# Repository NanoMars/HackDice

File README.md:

# HackDice

## Schematic

## PCB

## Features
- Animated Dice rolling animation
- Displays a random side of a 6 sided dice on a custom LED 7 segment display
- USB C powered

## BOM
- 7 	LED's
- 7 	220 Resistor
- 1 	Push Button
- 1   Seeed XIAO RP2040

Made by `@Mars` on slack :D

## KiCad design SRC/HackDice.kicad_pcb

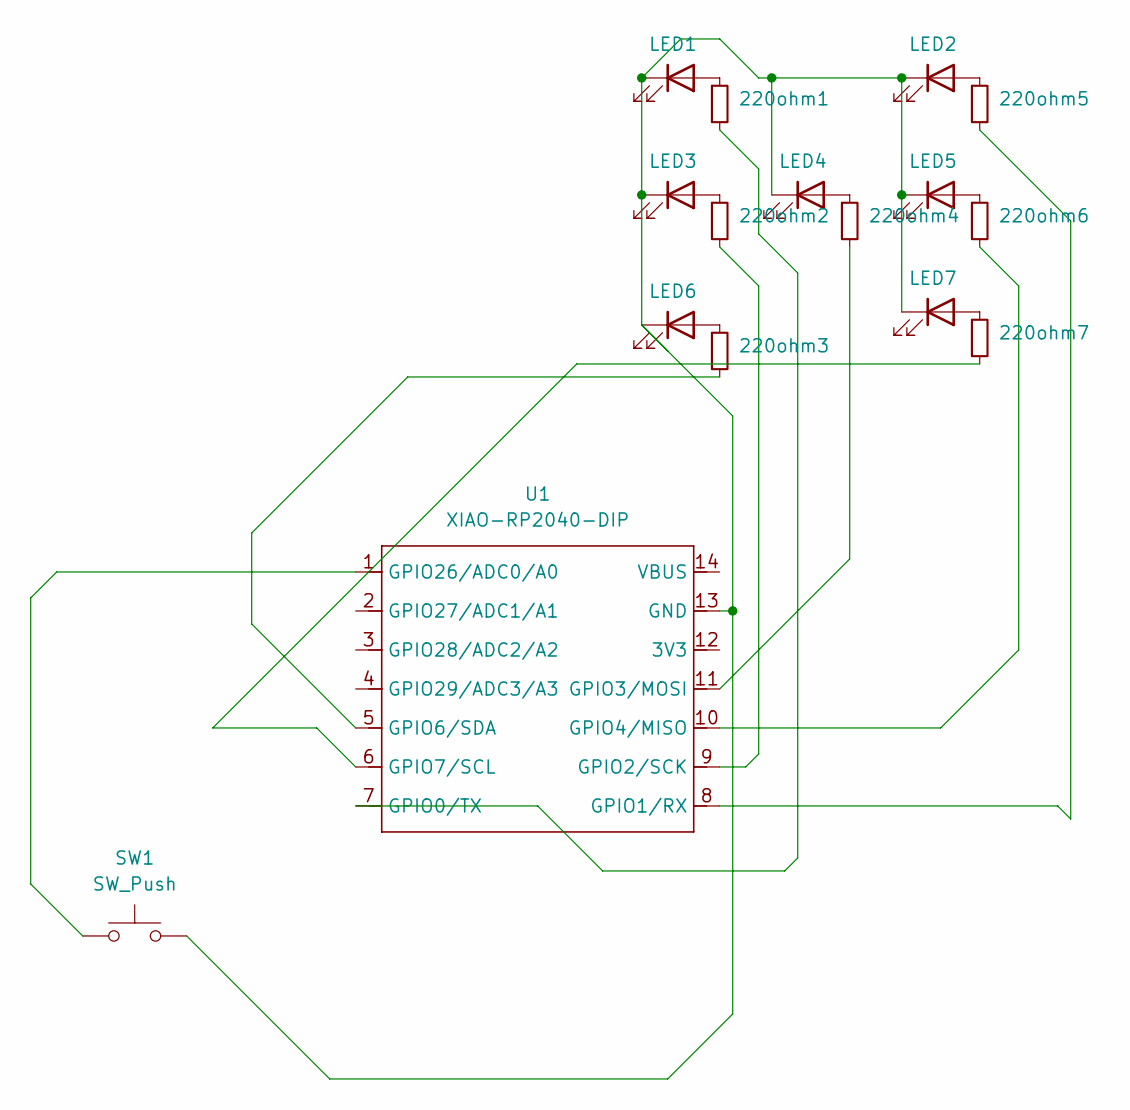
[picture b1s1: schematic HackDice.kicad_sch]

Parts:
220ohm1, 220ohm2, 220ohm3, 220ohm4, 220ohm5, 220ohm6, 220ohm7: R_Small; R_Axial_DIN0207_L6.3mm_D2.5mm_P7.62mm_Horizontal
LED1, LED2, LED3, LED4, LED5, LED6, LED7: LED; LED_D5.0mm
SW1: SW_Push; SW_PUSH_6mm
U1: XIAO-RP2040-DIP

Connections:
unnamed: 220ohm1.1, LED1.2 (A)
unnamed: LED1.1 (K), LED2.1 (K), LED3.1 (K), LED4.1 (K), LED5.1 (K), LED6.1 (K), LED7.1 (K), SW1.2, U1.13 (GND)
unnamed: 220ohm5.1, LED2.2 (A)
unnamed: 220ohm2.1, LED3.2 (A)
unnamed: 220ohm4.1, LED4.2 (A)
unnamed: 220ohm6.1, LED5.2 (A)
unnamed: 220ohm3.1, LED6.2 (A)
unnamed: 220ohm7.1, LED7.2 (A)
unnamed: 220ohm1.2, U1.7 (GPIO0/TX)
unnamed: 220ohm5.2, U1.8 (GPIO1/RX)
unnamed: 220ohm2.2, U1.9 (GPIO2/SCK)
unnamed: 220ohm4.2, U1.11 (GPIO3/MOSI)
unnamed: 220ohm6.2, U1.10 (GPIO4/MISO)
unnamed: 220ohm3.2, U1.5 (GPIO6/SDA)
unnamed: 220ohm7.2, U1.6 (GPIO7/SCL)
unnamed: SW1.1, U1.1 (GPIO26/ADC0/A0)

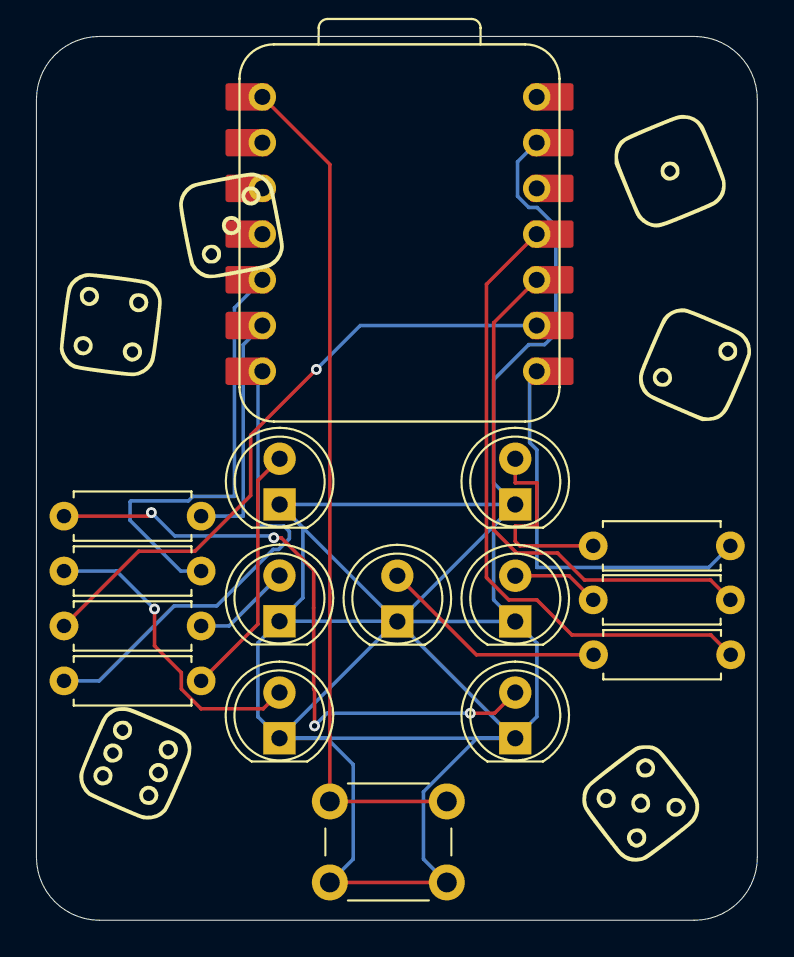
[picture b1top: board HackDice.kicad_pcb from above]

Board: 2 copper layers, 40.0 x 49.1 mm, 16 parts (0 on the bottom side), 16 nets.

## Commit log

2025-04-11 Added production files
